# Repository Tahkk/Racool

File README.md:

# 🦝 Racool — Innoserv Awards Contest

<div align="center">

</div>

## About

This repository hosts the hardware design presented at the *Innoserv Awards Contest*, held in October 2025 in Taiwan.

**Racool** is a compact PCB that estimates how many people are present in a closed space without cameras and without identifying anyone. It combines a 60 GHz radar for presence/occupancy sensing with a CO₂ / temperature / humidity sensor, all driven by an ESP32 microcontroller with Wi‑Fi and Bluetooth LE connectivity.

## Use cases

Racool is designed for any enclosed space where occupancy and air quality matter:

- Public transport (buses, trains, metros)
- Hospital and clinic waiting rooms
- Restaurants and cafés
- Gyms and fitness clubs
- Offices, meeting rooms, classrooms

## Key features

- **Anonymous by design**: radar sensing captures no images, no sound and no personal data.
- **Air-quality awareness**: real CO₂, temperature and humidity measurements.
- **Wireless**: Wi‑Fi and BLE for data reporting.
- **Compact & simple**: single board, powered and programmed over USB‑C.

## Hardware

- **ESP32‑C3‑WROOM‑02** : Main MCU with Wi‑Fi and BLE; runs the firmware and processes sensor data 
- **BGT60TR13C** (Infineon) : 60 GHz FMCW radar sensor used for presence / occupancy detection 
- **SCD41** (Sensirion) : Photoacoustic CO₂ sensor with integrated temperature and humidity sensing 
- **MP2232HGTL** : Power management 
- **USB‑C connector** : Programming and power supply 

## How it works

```
 ┌────────────┐  SPI   ┌──────────────┐        ┌────────────────┐
 │ BGT60TR13C │───────▶│              │  Wi‑Fi │  Cloud /       │
 │ (60 GHz)   │        │  ESP32‑C3    │───────▶│  dashboard     │
 └────────────┘        │              │  BLE   │  (optional)    │
 ┌────────────┐  I²C   │              │        └────────────────┘
 │   SCD41    │───────▶│              │
 │ CO₂/T/RH   │        └──────────────┘
 └────────────┘              ▲
                        USB‑C / power
```

1. The radar captures motion and micro-motion signatures in the room.
2. The MCU processes them to estimate occupancy.
3. The SCD41 provides CO₂, temperature and humidity readings.
4. Data is sent over Wi‑Fi/BLE to a dashboard or gateway.

## Layers and 3D view

<div align="center">
<br>
Top layer<br>

<br>
  Ground layer<br>
<br>
  Inside layer<br>
<br>
  Bottom layer<br>
</div>

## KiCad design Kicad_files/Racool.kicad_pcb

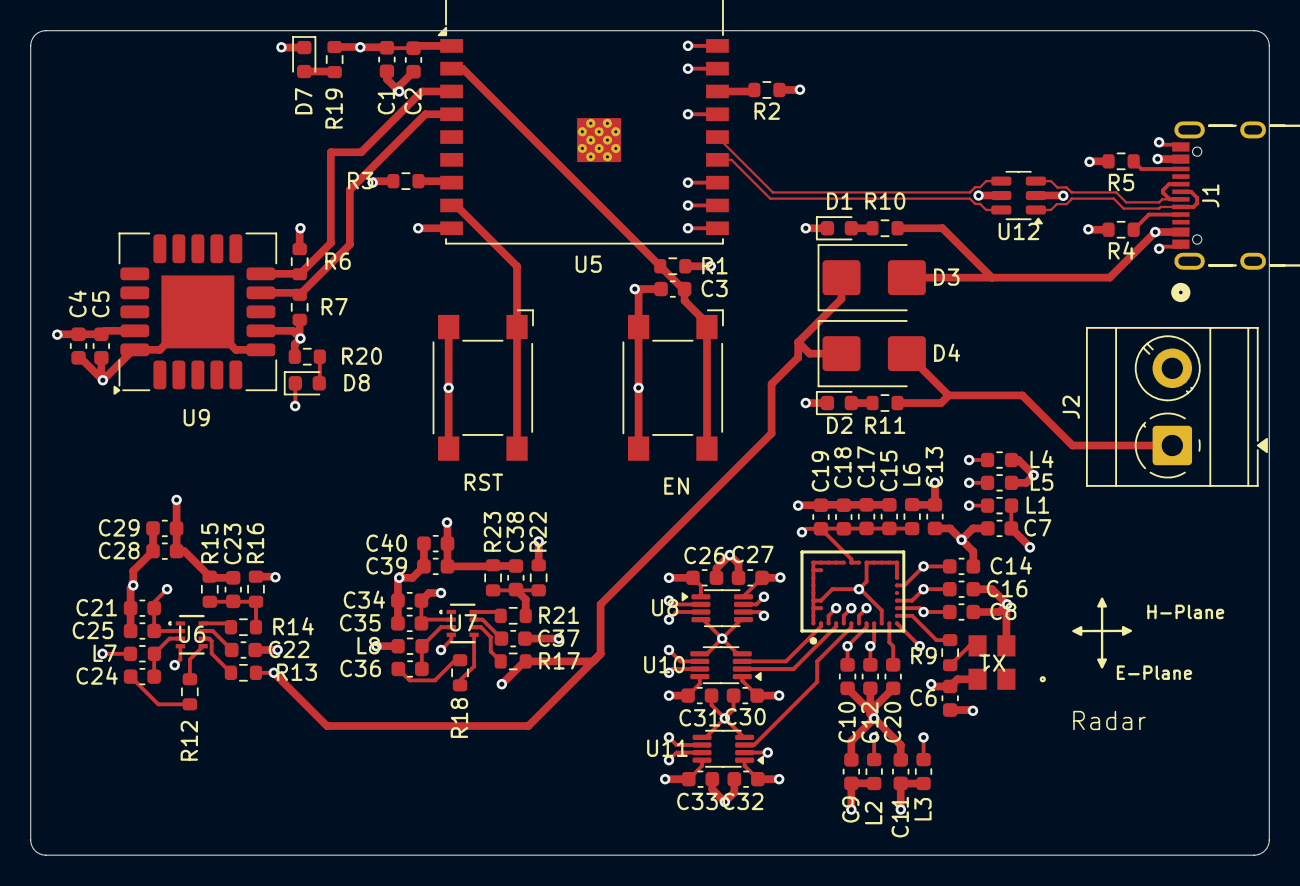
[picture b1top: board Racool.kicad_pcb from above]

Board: 4 copper layers, 81.5 x 54.2 mm, 90 parts (0 on the bottom side), 57 nets.

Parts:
C1, C4, C7, C9, C12, C13, C15, C22, C37: 10µF; C_0603_1608Metric
C2, C25, C26, C27, C30, C31, C32, C33, C35: 0.1µF; C_0603_1608Metric
C3, C8, C10, C14, C16, C17, C18, C19, C24, C36: 1µF; C_0603_1608Metric
C5, C11: 100nF; C_0603_1608Metric
C6: 0.01µF; C_0603_1608Metric
C20: 470nF; C_0603_1608Metric
C21, C28, C29, C34, C39, C40: 22µF; C_0603_1608Metric
C23, C38: 10pF; C_0603_1608Metric
D1: B_LED; LED_0603_1608Metric
D2, D7, D8: R_LED; LED_0603_1608Metric
D3, D4: MBRS130LT3; D_SMB
EN: SW_Omron_B3FS; SW_SPST_Omron_B3FS-100xP
J1: GT-USB-7004; CONN12_B-7004_GSW
J2: 5V; TerminalBlock_MetzConnect_Type073_RT02602HBLU_1x02_P5.08mm_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
L1, L2, L3, L4, L5, L6: L; L_0603_1608Metric
L7: 0.47µH; L_0603_1608Metric
L8: 0.68µH; L_0603_1608Metric
R1, R2, R3: 10k; R_0603_1608Metric
R4, R5: 5k1; R_0603_1608Metric
R6, R7: 4.7k; R_0603_1608Metric
R9: 150; R_0603_1608Metric
R10: 220; R_0603_1608Metric
R11: 300; R_0603_1608Metric
R12, R18: 20; R_0603_1608Metric
R13, R17: 120k; R_0603_1608Metric
R14, R15, R23: 40.2k; R_0603_1608Metric
R16: 13k; R_0603_1608Metric
R19, R20: 1k; R_0603_1608Metric
R21: 20k; R_0603_1608Metric
R22: 32.4k; R_0603_1608Metric
RST: SW_Omron_B3FS; SW_SPST_Omron_B3FS-100xP
U5: ESP32-C3-WROOM-02
U6, U7: MP2332HGTL-Z; SOT583_MP2332H_MNP
U8, U10, U11: SN74LVC2T45DCUR; VSSOP-8_2.3x2mm_P0.5mm
U9: SCD41-D-R2; Sensirion_SCD4x-1EP_10.1x10.1mm_P1.25mm_EP4.8x4.8mm
U12: USBLC6-2SC6; SOT-23-6
U$1: BGT60TR13C; BGA40N50P9X12_500X650X90-V
X1: TXC CORP 7X80000600; SON4_SIT8008_3p2x2p5_SIT

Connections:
1.8V: C6.1, C9.1, C11.1, C13.1, C27.1, C30.1, C32.1, C38.2, C39.1, C40.1, L2.1, L3.1, L4.1, L5.1, L6.1, L8.2, R23.2, U8.8 (VCCB), U10.1 (VCCA), U11.1 (VCCA), X1.4 (VDD)
3.3V: C1.1, C2.1, C4.1, C5.1, C7.1, C23.2, C26.1, C28.1, C29.1, C31.1, C33.1, L1.1, L7.2, R1.1, R2.1, R3.1, R6.1, R7.1, R15.2, R19.1, R20.1, U5.1 (3V3), U8.1 (VCCA), U9.7 (VDD), U9.19 (VDD), U10.8 (VCCB), U11.8 (VCCB)
/ESP32/CC1: J1.A5, R4.1
/ESP32/CC2: J1.B5, R5.1
/ESP32/D+: U5.14 (IO19), U12.4 (I/O2)
/ESP32/D-: U5.13 (IO18), U12.6 (I/O1)
/ESP32/EN: C3.1, EN.1, R1.2, U5.2 (EN)
/ESP32/Strap 08: R3.2, U5.7 (IO8)
/ESP32/Strap 09: RST.1, U5.8 (IO9)
/ESP32/Strap_02: R2.2, U5.16 (IO2)
/ESP32/USB_DN: J1.A7, J1.B7, U12.1 (I/O1)
/ESP32/USB_DP: J1.A6, J1.B6, U12.3 (I/O2)
/Radar/CLK: U10.3 (A2), U$1.B1 (CLK)
/Radar/CS_N: U11.2 (A1), U$1.G1 (CS_N)
/Radar/DI: U10.2 (A1), U$1.D1 (DI)
/Radar/DO: U8.6 (B2), U$1.E1 (DO)
/Radar/IRQ: U8.7 (B1), U$1.C1 (IRQ)
/Radar/OSC_CLK: R9.2, U$1.M2 (OSC_CLK)
/Radar/RST: U11.3 (A2), U$1.F1 (RST/DIO3_)
/Radar/VDD_A: C12.1, L3.2, U$1.J1 (VDDA)
/Radar/VDD_D: C10.1, L2.2, U$1.H1 (VDDD)
/Radar/VDD_LF: C8.1, L1.2, U$1.M3 (VDDLF)
/Radar/VDD_PLL: C16.1, L5.2, U$1.M4 (VDDPLL)
/Radar/VDD_RF: C15.1, C17.1, C18.1, C19.1, L6.2, U$1.F9 (VDDRF@1), U$1.G9 (VDDRF@2), U$1.M1 (VDDRF@3)
/Radar/VDD_VCO: C14.1, L4.2, U$1.M6 (VDDVCO)
GND: C1.2, C2.2, C3.2, C4.2, C5.2, C6.2, C7.2, C8.2, C9.2, C10.2, C11.2, C12.2, C13.2, C14.2, C15.2, C16.2, C17.2, C18.2, C19.2, C20.2, C21.2, C22.2, C25.2, C26.2, C27.2, C28.2, C29.2, C30.2, C31.2, C32.2, C33.2, C34.2, C35.2, C37.2, C39.2, C40.2, D1.1 (K), D2.1 (K), D7.1 (K), D8.1 (K), EN.2, J1.A1, J1.A12, J1.B1, J1.B12, J2.2, R4.2, R5.2, R16.2, R22.2, RST.2, U5.9 (GND), U5.19 (GND), U6.4 (GND), U7.4 (GND), U8.4 (GND), U8.5 (DIR), U9.6 (GND), U9.20 (GND), U9.21 (GND), U10.4 (GND), U10.5 (DIR), U11.4 (GND), U11.5 (DIR), U12.2 (GND), U$1.A1 (VSSD@1), U$1.A2 (VSSD@2), U$1.A3 (VSSRF@1), U$1.A4 (VSSRF@2), U$1.A5 (VSSRF@3), U$1.A6 (VSSRF@4), U$1.A7 (VSSRF@5), U$1.A8 (VSSRF@6), U$1.A9 (VSSRF@7), U$1.B3 (VSSRF@8), U$1.B4 (VSSRF@9), U$1.B8 (VSSRF@10), U$1.B9 (VSSRF@11), U$1.C9 (VSSRF@12), U$1.D9 (VSSRF@13), U$1.E9 (VSSRF@14), U$1.H9 (VSSRF@15), U$1.J9 (VSSRF@16), U$1.K1 (VSSA), U$1.K9 (VSSRF@17), U$1.L9 (VSSRF@18), U$1.M7 (VSSRF@19), U$1.M9 (VSSRF@20), X1.2 (GND)
IRQ_RADAR: U5.10 (IO10), U8.2 (A1)
unnamed: C23.1, R14.2, R15.1, R16.1
unnamed: C24.1, R12.2
unnamed: C36.1, R18.2
unnamed: C38.1, R21.2, R22.1, R23.1
unnamed: D1.2 (A), R10.2
unnamed: D2.2 (A), R11.2
unnamed: C21.1, C25.1, C34.1, C35.1, D3.1 (K), D4.1 (K), R13.1, R17.1, U6.2 (IN), U7.2 (IN)
unnamed: D4.2 (A), J2.1, R11.1
unnamed: D7.2 (A), R19.2
unnamed: D8.2 (A), R20.2
unnamed: R12.1, U6.5 (BST)
unnamed: R13.2, U6.6 (EN)
unnamed: R14.1, U6.8 (FB)
unnamed: C22.1, U6.7 (SS)
unnamed: C24.2, L7.1, U6.3 (SW)
unnamed: R18.1, U7.5 (BST)
unnamed: R17.2, U7.6 (EN)
unnamed: R21.1, U7.8 (FB)
unnamed: C37.1, U7.7 (SS)
unnamed: C36.2, L8.1, U7.3 (SW)
unnamed: C20.1, U$1.L1 (VAREF)
unnamed: R9.1, X1.3 (OUT)
RST_RADAR: U5.17 (IO1), U11.6 (B2)
SCL: R7.2, U5.4 (IO5), U9.9 (SCL)
SDA: R6.2, U5.3 (IO4), U9.10 (SDA)
SPI_CLK: U5.12 (IO21/TXD), U10.6 (B2)
SPI_MISO: U5.11 (IO20/RXD), U8.3 (A2)
SPI_MOSI: U5.15 (IO3), U10.7 (B1)
SPI_SELECT: U5.18 (IO0), U11.7 (B1)
VBUS: D3.2 (A), J1.A4, J1.A9, J1.B4, J1.B9, R10.1, U12.5 (VBUS)

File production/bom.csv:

Designator,Footprint,Quantity,Value,LCSC Part #
"C1, C12, C13, C15, C22, C37, C4, C7, C9",0603,9,10µF,
"C10, C14, C16, C17, C18, C19, C24, C3, C36, C8",0603,10,1µF,
"C11, C5",0603,2,100nF,
"C2, C25, C26, C27, C30, C31, C32, C33, C35",0603,9,0.1µF,
C20,0603,1,470nF,
"C21, C28, C29, C34, C39, C40",0603,6,22µF,
"C23, C38",0603,2,10pF,
C6,0603,1,0.01µF,
D1,0603,1,B_LED,
"D2, D7, D8",0603,3,R_LED,
"D3, D4",D_SMB,2,MBRS130LT3,
"EN, RST",SW_SPST_Omron_B3FS-100xP,2,SW_Omron_B3FS,
J1,CONN12_B-7004_GSW,1,GT-USB-7004,
J2,TerminalBlock_MetzConnect_Type073_RT02602HBLU_1x02_P5.08mm_Horizontal,1,5V,
"L1, L2, L3, L4, L5, L6",0603,6,L,
L7,0603,1,0.47µH,
L8,0603,1,0.68µH,
"R1, R2, R3",0603,3,10k,
R10,0603,1,220,
R11,0603,1,300,
"R12, R18",0603,2,20,
"R13, R17",0603,2,120k,
"R14, R15, R23",0603,3,40.2k,
R16,0603,1,13k,
"R19, R20",0603,2,1k,
R21,0603,1,20k,
R22,0603,1,32.4k,
"R4, R5",0603,2,5k1,
"R6, R7",0603,2,4.7k,
R9,0603,1,150,
U$1,BGA40N50P9X12_500X650X90-V,1,BGT60TR13C,
"U10, U11, U8",VSSOP-8_2.3x2mm_P0.5mm,3,SN74LVC2T45DCUR,
U12,SOT-23-6,1,USBLC6-2SC6,
U5,ESP32-C3-WROOM-02,1,ESP32-C3-WROOM-02,
"U6, U7",SOT583_MP2332H_MNP,2,MP2332HGTL-Z,
U9,Sensirion_SCD4x-1EP_10.1x10.1mm_P1.25mm_EP4.8x4.8mm,1,SCD41-D-R2,
X1,SON4_SIT8008_3p2x2p5_SIT,1,TXC CORP 7X80000600,
